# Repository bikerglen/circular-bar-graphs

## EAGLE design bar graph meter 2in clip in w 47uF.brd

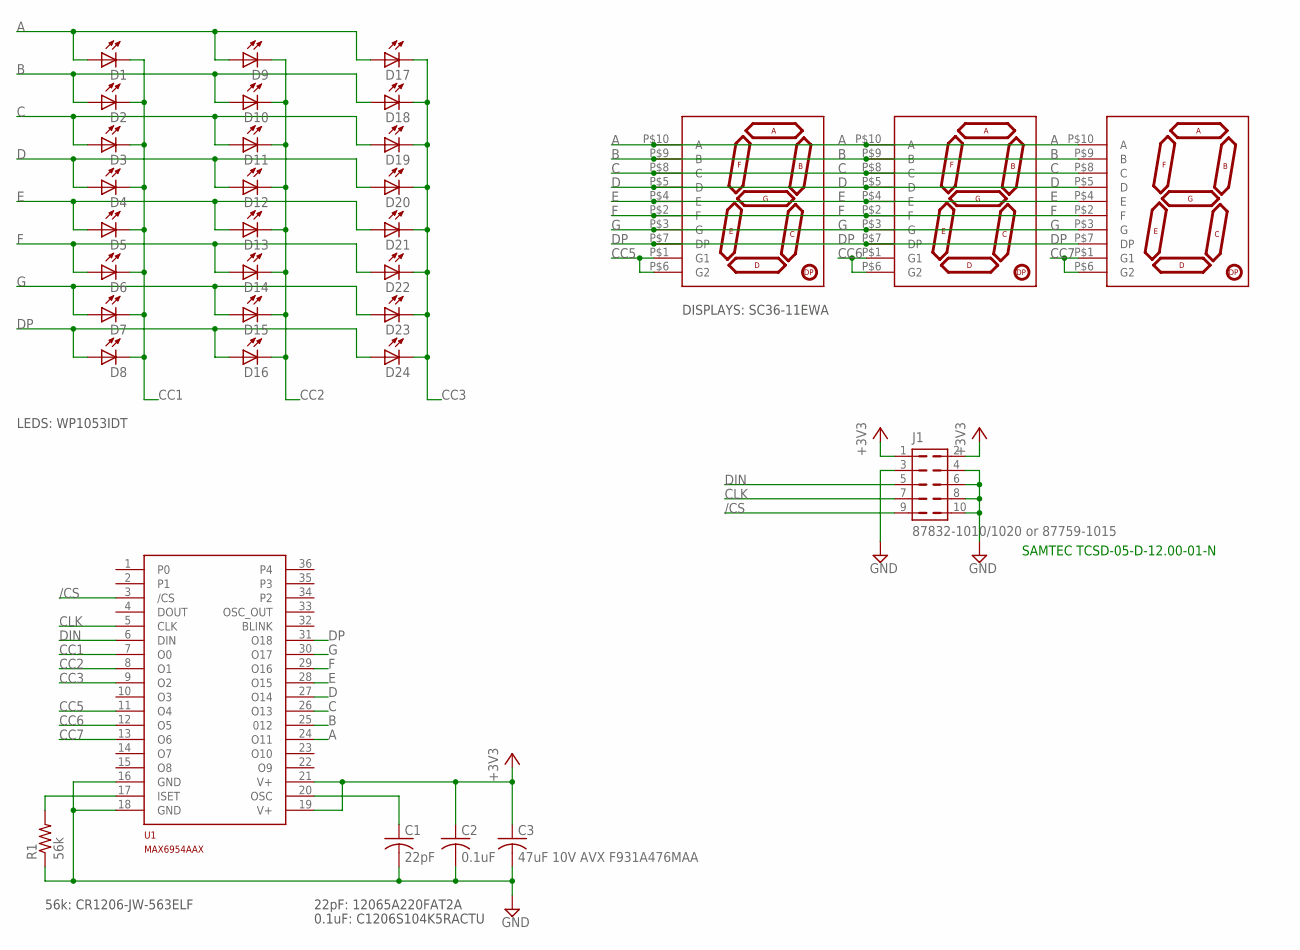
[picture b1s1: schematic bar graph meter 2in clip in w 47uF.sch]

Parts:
C1: 22pF; C1206
C2: 0.1uF; C1206
C3: 47uF 10V AVX F931A476MAA; C1206
D1, D2, D3, D4, D5, D6, D7, D8, D9, D10, D11, D12, D13, D14, D15, D16, D17, D18, D19, D20, D21, D22, D23, D24: LEDSQR2X5; LED2X5
D25, D26, D27: SC36-11EWA; SA36-11
J1: 87832-1010/1020 or 87759-1015; 87832-10
R1: 56k; R1206
U1: MAX6954AAX; MAXIM-0.8-SSOP36

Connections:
+3V3: C2.1, C3.1, J1.1, J1.2, U1.19 (V+), U1.21 (V+)
/CS: J1.9, U1.3 (/CS)
A: D1.A, D9.A, D17.A, D25.P$10 (A), D26.P$10 (A), D27.P$10 (A), U1.24 (O11)
B: D2.A, D10.A, D18.A, D25.P$9 (B), D26.P$9 (B), D27.P$9 (B), U1.25 (012)
C: D3.A, D11.A, D19.A, D25.P$8 (C), D26.P$8 (C), D27.P$8 (C), U1.26 (O13)
CC1: D1.K (C), D2.K (C), D3.K (C), D4.K (C), D5.K (C), D6.K (C), D7.K (C), D8.K (C), U1.7 (O0)
CC2: D9.K (C), D10.K (C), D11.K (C), D12.K (C), D13.K (C), D14.K (C), D15.K (C), D16.K (C), U1.8 (O1)
CC3: D17.K (C), D18.K (C), D19.K (C), D20.K (C), D21.K (C), D22.K (C), D23.K (C), D24.K (C), U1.9 (O2)
CC5: D25.P$1 (G1), D25.P$6 (G2), U1.11 (O4)
CC6: D26.P$1 (G1), D26.P$6 (G2), U1.12 (O5)
CC7: D27.P$1 (G1), D27.P$6 (G2), U1.13 (O6)
CLK: J1.7, U1.5 (CLK)
CSET: C1.1, U1.20 (OSC)
D: D4.A, D12.A, D20.A, D25.P$5 (D), D26.P$5 (D), D27.P$5 (D), U1.27 (O14)
DIN: J1.5, U1.6 (DIN)
DP: D8.A, D16.A, D24.A, D25.P$7 (DP), D26.P$7 (DP), D27.P$7 (DP), U1.31 (O18)
E: D5.A, D13.A, D21.A, D25.P$4 (E), D26.P$4 (E), D27.P$4 (E), U1.28 (O15)
F: D6.A, D14.A, D22.A, D25.P$2 (F), D26.P$2 (F), D27.P$2 (F), U1.29 (O16)
G: D7.A, D15.A, D23.A, D25.P$3 (G), D26.P$3 (G), D27.P$3 (G), U1.30 (O17)
GND: C1.2, C2.2, C3.2, J1.3, J1.4, J1.6, J1.8, J1.10, R1.1, U1.16 (GND), U1.18 (GND)
ISET: R1.2, U1.17 (ISET)

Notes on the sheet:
SAMTEC TCSD-05-D-12.00-01-N
LEDS: WP1053IDT
DISPLAYS: SC36-11EWA
22pF: 12065A220FAT2A
0.1uF: C1206S104K5RACTU
56k: CR1206-JW-563ELF

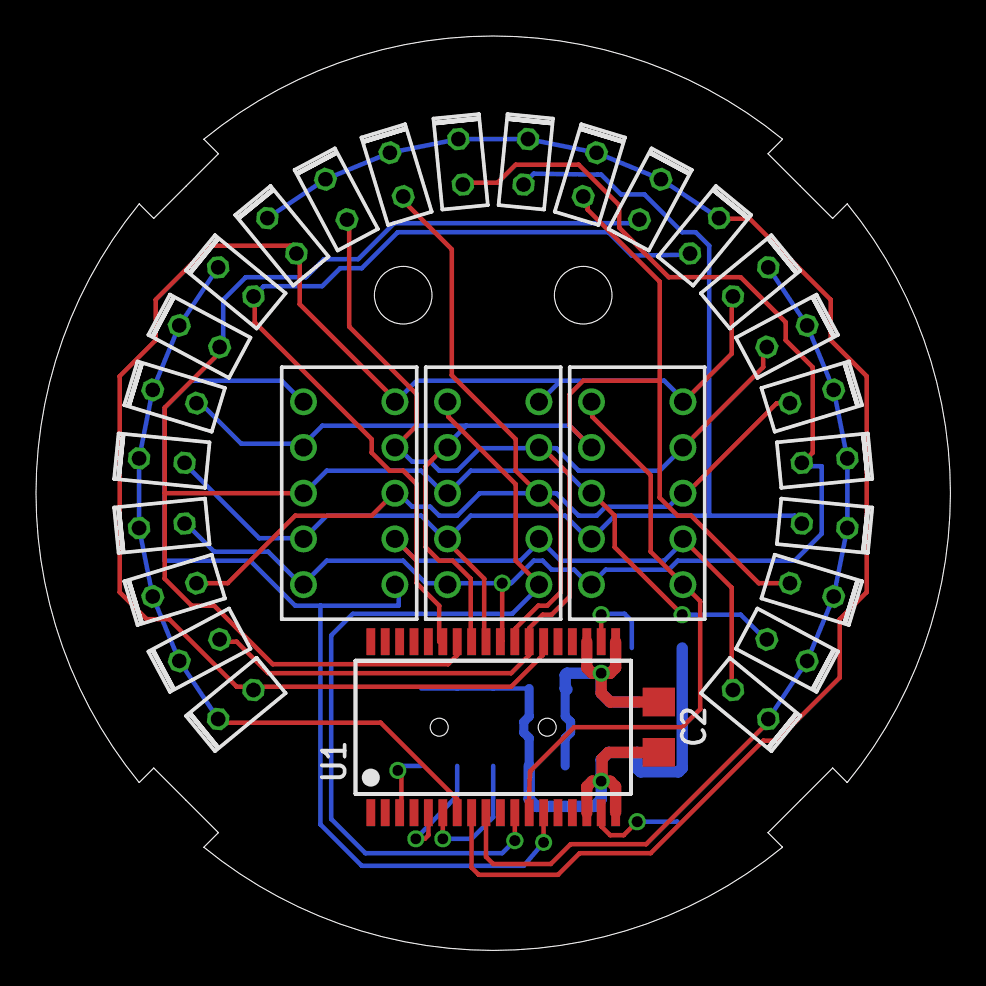
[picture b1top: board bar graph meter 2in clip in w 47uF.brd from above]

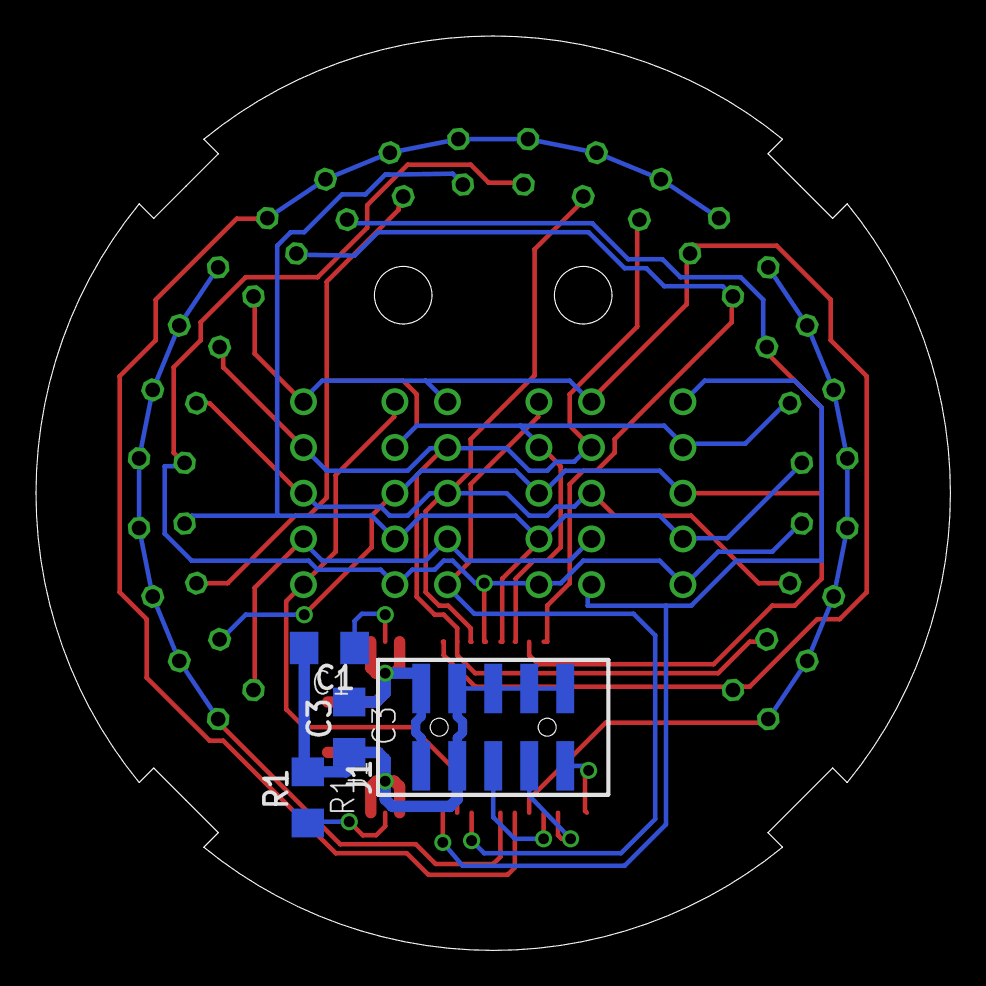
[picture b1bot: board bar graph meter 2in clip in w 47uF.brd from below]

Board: 2 copper layers, 50.8 x 50.8 mm, 33 parts (4 on the bottom side), 21 nets.

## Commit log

2017-04-29 initial checkin
2017-08-19 added bar graph mounting bracket
